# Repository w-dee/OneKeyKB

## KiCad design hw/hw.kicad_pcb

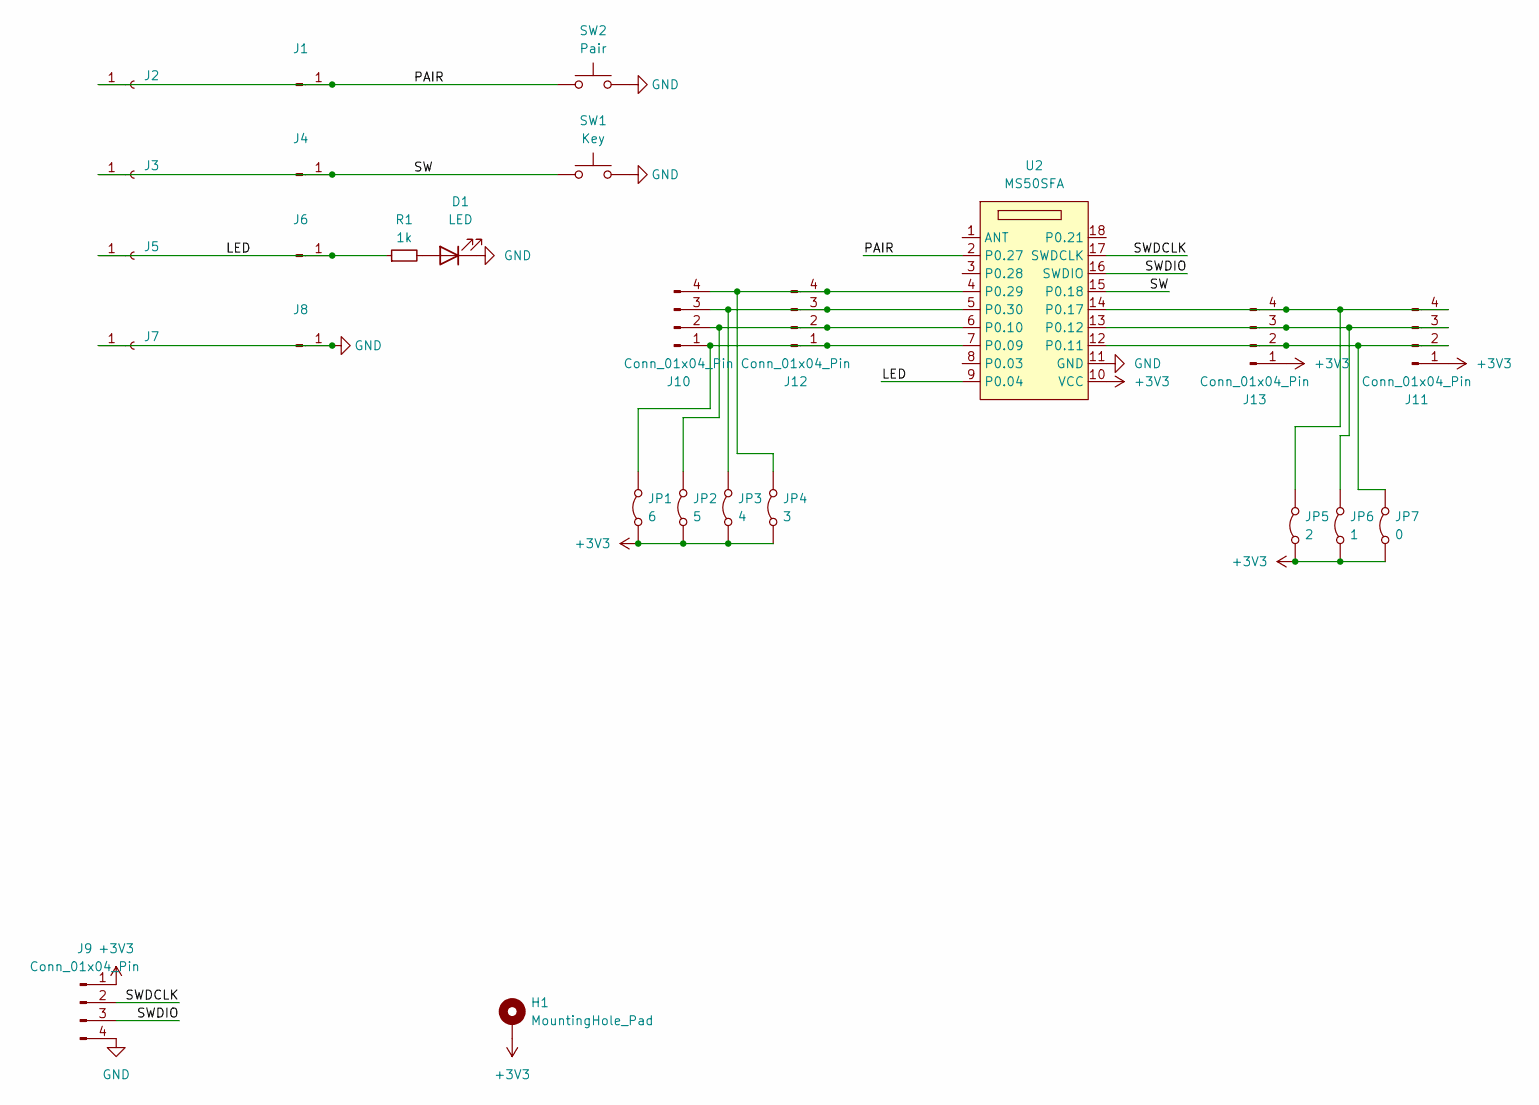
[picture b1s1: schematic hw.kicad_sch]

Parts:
D1: LED; LED_0603_1608Metric_Pad1.05x0.95mm_HandSolder
H1: MountingHole_Pad; finger_hole_8.0x0.8
J1, J4, J6, J8: Conn_01x02_Pin; PinHeader_1x01_P2.54mm_Vertical
J2, J3, J5, J7: Conn_01x02_Socket; PinSocket_1x01_P2.54mm_Vertical
J9, J10, J11: Conn_01x04_Pin; PinHeader_1x04_P2.54mm_Vertical
J12, J13: Conn_01x04_Pin; PinSocket_1x04_P2.54mm_Vertical
JP1: 6; SolderJumper-2_P1.3mm_Open_RoundedPad1.0x1.5mm
JP2: 5; SolderJumper-2_P1.3mm_Open_RoundedPad1.0x1.5mm
JP3: 4; SolderJumper-2_P1.3mm_Open_RoundedPad1.0x1.5mm
JP4: 3; SolderJumper-2_P1.3mm_Open_RoundedPad1.0x1.5mm
JP5: 2; SolderJumper-2_P1.3mm_Open_RoundedPad1.0x1.5mm
JP6: 1; SolderJumper-2_P1.3mm_Open_RoundedPad1.0x1.5mm
JP7: 0; SolderJumper-2_P1.3mm_Open_RoundedPad1.0x1.5mm
R1: 1k; R_0603_1608Metric_Pad0.98x0.95mm_HandSolder
SW1: Key; SW_Cherry_MX_1.00u_PCB
SW2: Pair; TACT_SW_SMD_Panasonic-EVPAWBD2A
U2: MS50SFA

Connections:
+3V3: H1.1, J9.1, J11.1, J13.1, JP1.1 (A), JP2.1 (A), JP3.1 (A), JP4.1 (A), JP5.1 (A), JP6.1 (A), JP7.1 (A), U2.10 (VCC)
/LED: J5.1, J6.1, R1.1, U2.9 (P0.04)
/PAIR: J1.1, J2.1, SW2.1, U2.2 (P0.27)
/SW: J3.1, J4.1, SW1.1, U2.15 (P0.18)
/SWDCLK: J9.2, U2.17 (SWDCLK)
/SWDIO: J9.3, U2.16 (SWDIO)
GND: D1.1 (K), J7.1, J8.1, J9.4, SW1.2, SW2.2, U2.11 (GND)
unnamed: D1.2 (A), R1.2
unnamed: J10.1, J12.1, JP1.2 (B), U2.7 (P0.09)
unnamed: J10.2, J12.2, JP2.2 (B), U2.6 (P0.10)
unnamed: J10.3, J12.3, JP3.2 (B), U2.5 (P0.30)
unnamed: J10.4, J12.4, JP4.2 (B), U2.4 (P0.29)
unnamed: J11.2, J13.2, JP7.2 (B), U2.12 (P0.11)
unnamed: J11.3, J13.3, JP6.2 (B), U2.13 (P0.12)
unnamed: J11.4, J13.4, JP5.2 (B), U2.14 (P0.17)

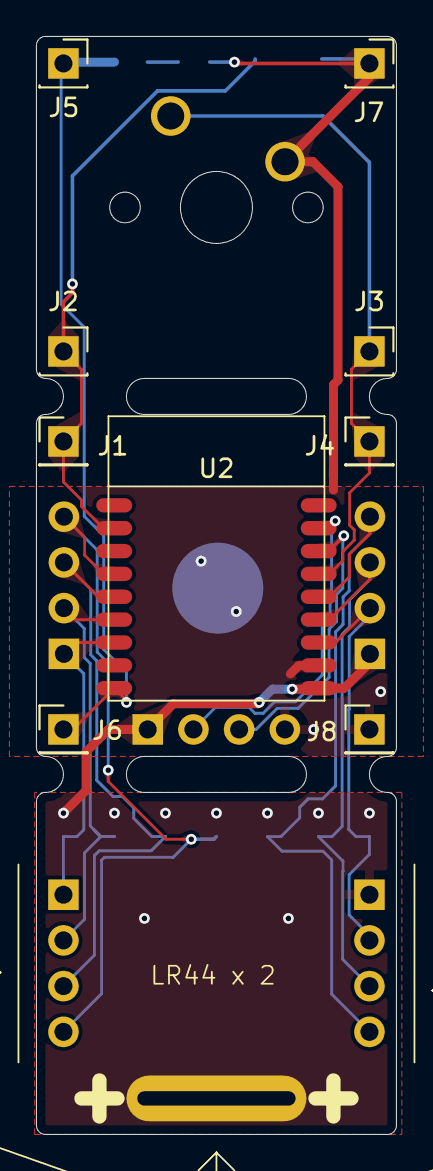
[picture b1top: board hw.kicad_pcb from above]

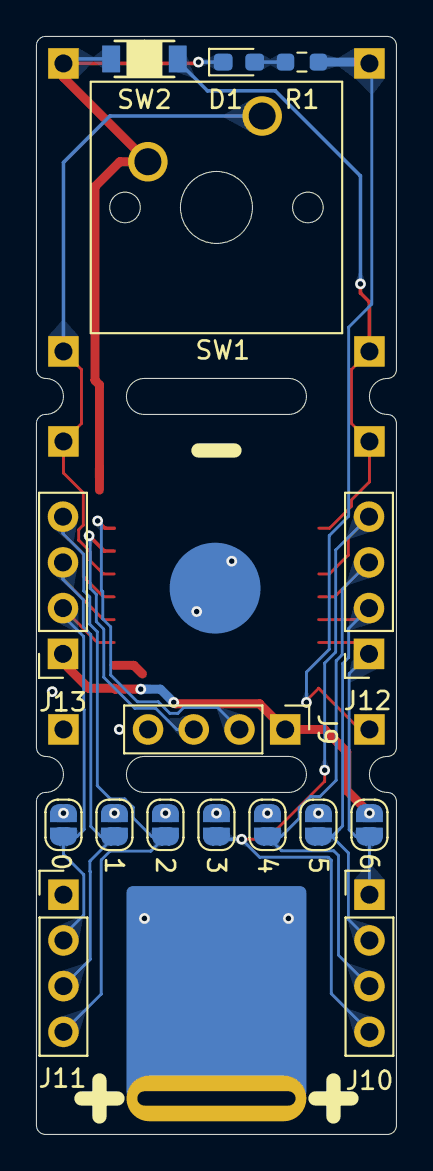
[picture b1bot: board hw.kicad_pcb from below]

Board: 2 copper layers, 20.0 x 61.0 mm, 26 parts (17 on the bottom side), 15 nets.

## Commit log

2024-12-21 Removed unneeded codes
2024-12-23 Retrieve key code from the "DIPSW"ain.c
